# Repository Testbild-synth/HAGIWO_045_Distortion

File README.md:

# HAGIWO Diode Distortion Eurorack Module

Through-hole 4HP  PCB version of the HAGIWO distortion eurorack module. 

### Current Status: Confirmed working.

## Hardware and PCB

You can find the schematic and BOM in the root folder. 
For the PCBs, the module has one circuit PCB and one panel PCB. 
You can order them on any common PCB manufacturing service, I used JLCPCB. For the circuit PCB, standard settings should be fine.
For the panel, since it has copper exposed, make sure to choose a lead free surface finish (LeadFree HASL, ENIG) and/or spraypaint your panels so that you don't get lead on your hands.

Build is super straight forward, but the 250K Pots specified by HAGIWO can be hard to source. I just used 1M instead, which probably changes how gain and distortion 
behave, but it still works so you can try that instead if you have a hard time sourcing 250k.

## Ideas

One Idea (that I did not try yet but definitely want to) is to exchange the 1n4148 diodes for header sockets or something so you can put in LEDs. Different color LEDs will produce different sound!

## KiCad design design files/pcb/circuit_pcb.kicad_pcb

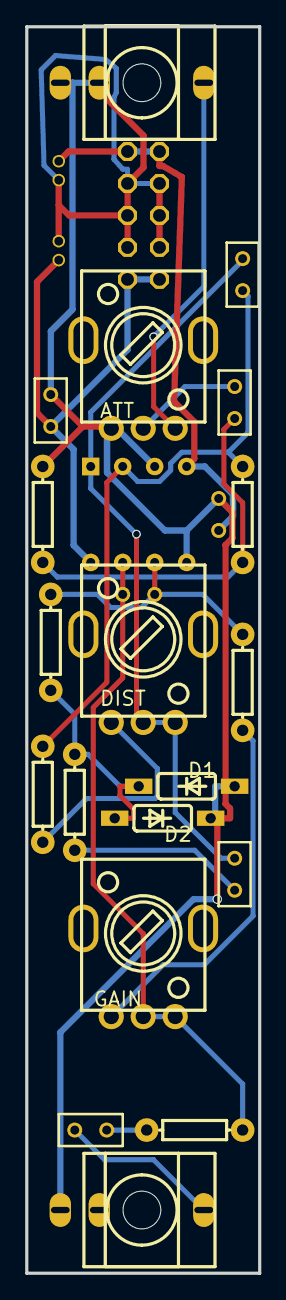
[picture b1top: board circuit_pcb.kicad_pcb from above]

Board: 2 copper layers, 18.5 x 99.0 mm, 25 parts (0 on the bottom side), 16 nets.

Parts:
ATT: 10k; R09-5KΩ
C1, C6: 100p; RAD-0.1
C2, C5, C7: 1u; RAD-0.1
C3, C4: 10u; CAP-D4.0×F1.5
C8, C9: 100n; RAD-0.1
D1, D2: 1n4148; DO35-7
DIST: 250k; R09-5KΩ
EP1: EURORACK_POWERHEADER_V2; EURORACK_POWER_V2
GAIN: 250k; R09-5KΩ
J1: IN; THONKICONN_1
J2: OUT; THONKICONN_1
R1, R3, R4: 4k7; R_AXIAL-0.3
R2, R5: 10k; R_AXIAL-0.3
R6: 1k; R_AXIAL-0.3
R14: 1M; R_AXIAL-0.3
U1: TL072BCP; DIP8

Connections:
12V: C4.1, C9.2, EP1.12, U1.8
-12V: C3.2, C8.1, EP1.-12, U1.4
ATT_2: ATT.2, C2.1
ATT_3: ATT.3, J1.3
C2_2: C2.2, R1.2, R14.2
C5_2: C5.2, R3.2
C7_1: C7.1, R6.1
C7_2: C7.2, J2.3
GAIN_1: GAIN.1, R5.1
GND: ATT.1, C3.1, C4.2, C8.2, C9.1, D1.A, D2.C, EP1.GND0, EP1.GND1, EP1.GND2, EP1.GND3, EP1.GND4, EP1.GND5, J1.1, J1.2, J2.1, R14.1, U1.3, U1.5
R2_1: DIST.1, R2.1
R3_1: D1.C, D2.A, R3.1, R4.2
U1_1: C1.2, C5.1, DIST.2, DIST.3, U1.1
U1_2: C1.1, R1.1, R2.2, U1.2
U1_6: C6.1, R4.1, R5.2, U1.6
U1_7: C6.2, GAIN.2, GAIN.3, R6.2, U1.7

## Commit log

2022-03-16 panel upload
2022-04-01 updload pcb files
2022-04-01 upload bom
